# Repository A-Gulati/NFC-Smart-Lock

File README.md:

# NFC-Smart-Lock

This project focuses on developing an NFC Smart Lock System that utilizes a smart phone’s onboard NFC chip as a method to unlock a door. Access is regulated using a central server which runs a simple user interface that allows an administrator to grant or deny entry to any particular user. The smart lock PCB interfaces with the server via a Wi-Fi module communicating with the TCP/IP protocol.
The goal for this project was to prototype a simple, reliable, and convenient lock mechanism that adds functionality to existing locks by integrating modern technology with the ancient and pervasive concept of door locks. This report details the design, testing, and conclusions that resulted from working toward accomplishing the aforementioned objectives.

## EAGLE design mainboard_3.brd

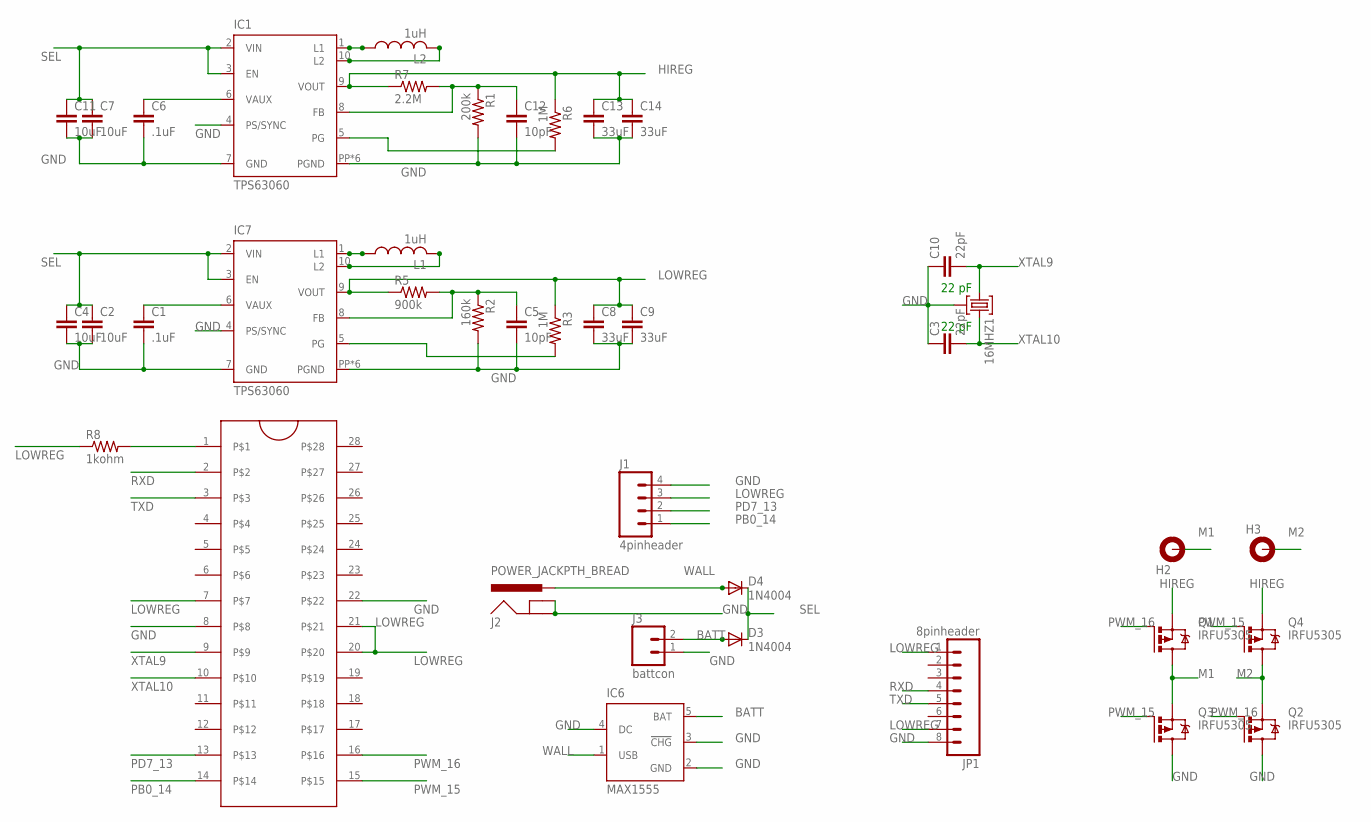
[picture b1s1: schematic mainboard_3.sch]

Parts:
16MHZ1: HC49-HC49-3L; HC49-3L
C1, C6: .1uF; C0805
C2, C4, C7, C11: 10uF; C3216
C3, C10: 22pF; C0805
C5, C12: 10pF; C1206
C8, C9, C13, C14: 33uF; C3216
D3, D4: 1N4004; DO41-10
H2, H3: MOUNT-PAD-ROUND4.1; 4,1-PAD
IC1, IC7: TPS63060; DSC-S-PWSON-N10
IC6: MAX1555; SOT23-5L
J1: 4pinheader; 1X04_LONGPADS
J2: POWER_JACKPTH_BREAD; POWER_JACK_PTH_BREAD
J3: battcon; JST-2-PTH-VERT
JP1: 8pinheader; 1X08_LONGPADS
L1, L2: 1uH; L4532P
Q1, Q2, Q3, Q4: IRFU5305; I-PAK_TO251AA
R1: 200k; M0805
R2: 160k; M0805
R3, R6: 1M; M0805
R5: 900k; M3216
R7: 2.2M; M3216
R8: 1kohm; M0805
U$1: ZIFSOCKET-28-3ZIFFSOCKET-28-3; DIL28-3-ZIF_SOCKET

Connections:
BATT: D3.A, IC6.5 (BAT), J3.2
GND: 16MHZ1.2, C1.2, C2.2, C3.1, C4.2, C5.2, C6.2, C7.2, C8.2, C9.2, C10.1, C11.2, C12.2, C13.2, C14.2, IC1.4 (PS/SYNC), IC1.7 (GND), IC1.PP (PGND), IC1.PP@1 (PGND), IC1.PP@2 (PGND), IC1.PP@3 (PGND), IC1.PP@4 (PGND), IC1.PP@7 (PGND), IC6.2 (GND), IC6.3 (!CHG), IC6.4 (DC), IC7.4 (PS/SYNC), IC7.7 (GND), IC7.PP (PGND), IC7.PP@1 (PGND), IC7.PP@2 (PGND), IC7.PP@3 (PGND), IC7.PP@4 (PGND), IC7.PP@7 (PGND), J1.4, J2.GND, J2.GNDBREAK, J3.1, JP1.8, Q2.2 (D), Q3.2 (D), R1.2, R2.2, U$1.8, U$1.22
HIREG: C13.1, C14.1, IC1.9 (VOUT), Q1.3 (S), Q4.3 (S), R6.1, R7.1
LOWREG: C8.1, C9.1, IC7.9 (VOUT), J1.3, JP1.1, JP1.7, R3.1, R5.1, R8.1, U$1.7, U$1.20, U$1.21
M1: H2.B4,1, Q1.2 (D), Q3.3 (S)
M2: H3.B4,1, Q2.3 (S), Q4.2 (D)
unnamed: R8.2, U$1.1
unnamed: IC1.1 (L1), L2.1
unnamed: IC7.1 (L1), L1.1
unnamed: IC7.10 (L2), L1.2
unnamed: IC1.10 (L2), L2.2
unnamed: C5.1, IC7.8 (FB), R2.1, R5.2
unnamed: C12.1, IC1.8 (FB), R1.1, R7.2
unnamed: C1.1, IC7.6 (VAUX)
unnamed: IC1.5 (PG), R6.2
unnamed: IC7.5 (PG), R3.2
unnamed: C6.1, IC1.6 (VAUX)
PB0_14: J1.1, U$1.14
PD7_13: J1.2, U$1.13
PWM_15: Q3.1 (G), Q4.1 (G), U$1.15
PWM_16: Q1.1 (G), Q2.1 (G), U$1.16
RXD: JP1.4, U$1.2
SEL: C2.1, C4.1, C7.1, C11.1, D3.C, D4.C, IC1.2 (VIN), IC1.3 (EN), IC7.2 (VIN), IC7.3 (EN)
TXD: JP1.5, U$1.3
WALL: D4.A, IC6.1 (USB), J2.PWR
XTAL9: 16MHZ1.1, C10.2, U$1.9
XTAL10: 16MHZ1.3, C3.2, U$1.10

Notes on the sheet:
22 pF

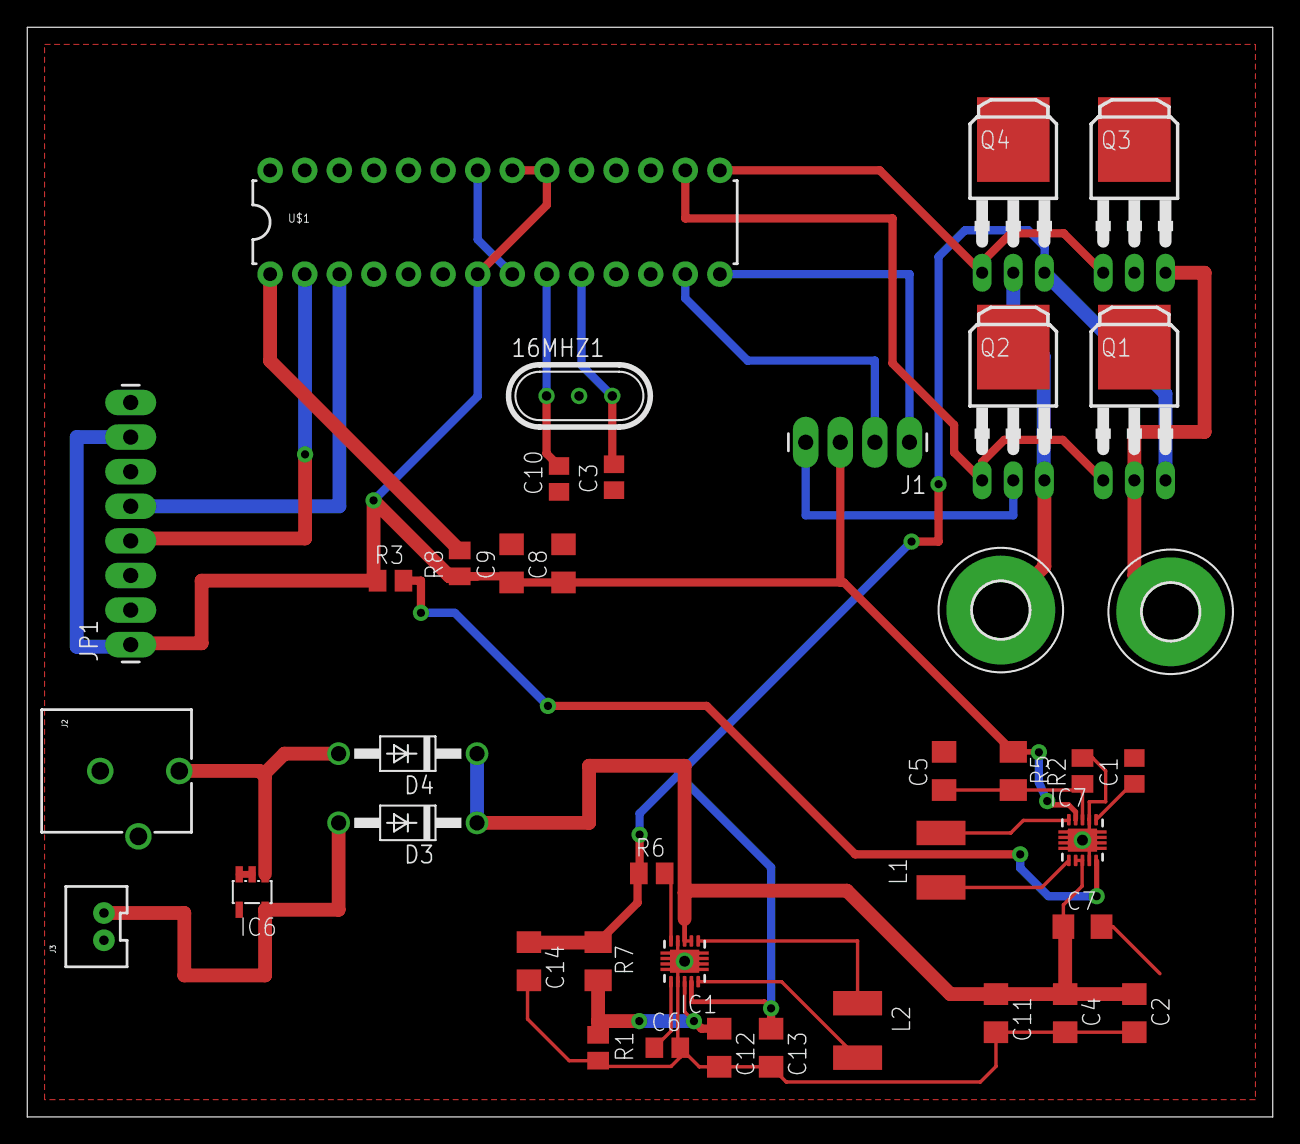
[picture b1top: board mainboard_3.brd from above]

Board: 2 copper layers, 91.4 x 80.0 mm, 40 parts (0 on the bottom side), 27 nets.

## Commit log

2017-12-27 Project Design Report
2017-12-27 NFC schematic and board files
    Software: EagleCAD

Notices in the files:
parts and their libraries:
SparkFun-Connectors: Licensing: Creative Commons ShareAlike 4.0 International - https://creativecommons.org/licenses/by-sa/4.0
